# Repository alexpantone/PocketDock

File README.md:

# PocketDock
The Pocket Dock modular synthesizer system and associated modules

Licensed under CERN-OHL-P-2.0

The base Pocket Dock is designed to take the +/-12v audio and control voltage of a Eurorack or Pocket Rack synthesizer system and safely shift them down to interface with a Pocket Operator, while giving it a nice little cradle to sit in a modular system. I've also made other modules to fit the Pocket Rack standard. These are all still very much in progress. The Dock is based on interfacing with the Pocket Operator via pogo pins, but that has not proved to be reliable in testing; I'm looking for better solutions.

Here's a rundown of the modules.
## Power Distro
#### Not tested
Provide Molex connectors to split power to other Pocket Rack modules, with reverse polarity protection.
## Buffered Mult
#### Tested: works great
two 1-to-3 buffered multipliers in one module. The second input is normaled to the first, so when nothing is connected to Input 2, it acts as a 1-to-6 mult. This module also doubles as an unbuffered passive mult by not populating any components besides the jacks and closing all the solder jumpers.
## Clock Skipper
#### Tested: works on a breadboard, current PCB version has no audio output
A simple version of a gate sequencer that uses an incoming clock signal, and mutes or unmutes the signal based on a small bank of DIP switches.
##Noise Hits
#### Not tested
White, pink, and blue noise generator with a simple transistor VCA on each channel to act as a simple drum machine.
## Nyblcore and Pikocore
#### My PCBs are untested
A version of Infinite Digit's [Nyblcore](https://github.com/schollz/nyblcore) and [Pikocore](https://infinitedigits.co/docs/products/pikocore/) refactored into the Pocket Rack size.
## Pocket Socket
#### Not tested
A base for prototyping new modules. All the jacks and power circuitry are on the main module, and the actual audio passes onto a daughterboard with pin headers.
## Quant
#### Not tested
a Seeed Studio Xiao-based quantizer. I haven't started the firmware on this yet.

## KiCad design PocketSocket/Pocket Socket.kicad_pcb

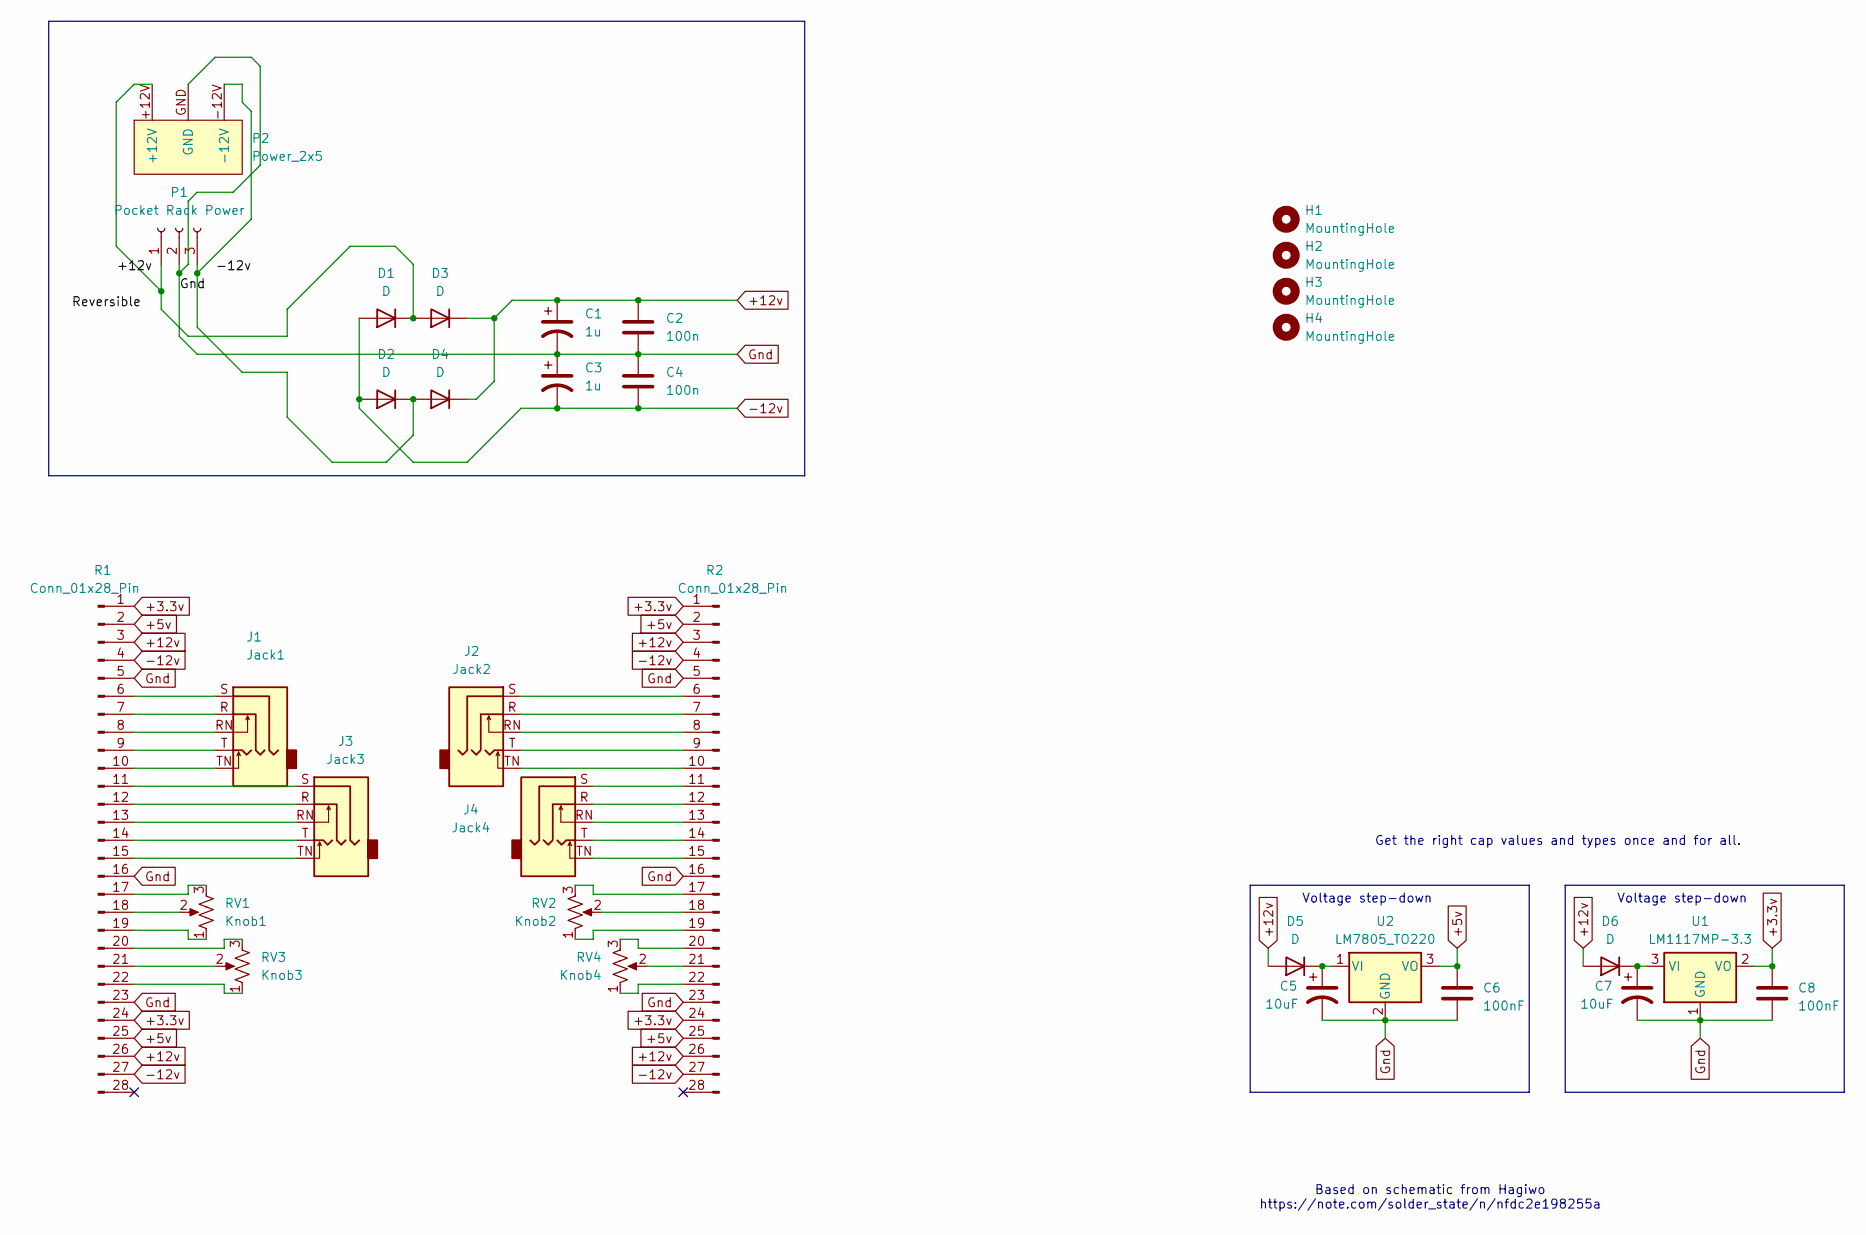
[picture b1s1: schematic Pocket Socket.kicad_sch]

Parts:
C1, C3: 1u; CP_EIA-3216-10_Kemet-I_Pad1.58x1.35mm_HandSolder
C2, C4: 100n; C_0805_2012Metric_Pad1.18x1.45mm_HandSolder
C5, C7: 10uF; C_0805_2012Metric_Pad1.18x1.45mm_HandSolder
C6, C8: 100nF; C_0805_2012Metric_Pad1.18x1.45mm_HandSolder
D1, D2, D3, D4, D5, D6: D; D_0805_2012Metric_Pad1.15x1.40mm_HandSolder
H1, H2, H3, H4: MountingHole; MountingHole_2.2mm_M2
J1: Jack1; Jack_3.5mm_QingPu_WQP-PJ358
J2: Jack2; Jack_3.5mm_QingPu_WQP-PJ358
J3: Jack3; Jack_3.5mm_QingPu_WQP-PJ358
J4: Jack4; Jack_3.5mm_QingPu_WQP-PJ358
P1: Pocket Rack Power; Molex_SL_171971-0003_1x03_P2.54mm_Vertical
P2: Power_2x5; Power_2x5_Vertical
R1, R2: Conn_01x28_Pin; PinHeader_1x28_P2.54mm_Vertical
RV1: Knob1; Potentiometer_Alpha_RD901F-40-00D_Single_Vertical
RV2: Knob2; Potentiometer_Alpha_RD901F-40-00D_Single_Vertical
RV3: Knob3; Potentiometer_Alpha_RD901F-40-00D_Single_Vertical
RV4: Knob4; Potentiometer_Alpha_RD901F-40-00D_Single_Vertical
U1: LM1117MP-3.3; SOT-223-3_TabPin2
U2: LM7805_TO220; SOT-223-3_TabPin2

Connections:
+3.3v: C8.1, R1.1, R1.24, R2.1, R2.24, U1.2 (VO)
+5v: C6.1, R1.2, R1.25, R2.2, R2.25, U2.3 (VO)
+12v: C1.1, C2.1, D3.1 (K), D4.1 (K), D5.2 (A), D6.2 (A), R1.3, R1.26, R2.3, R2.26
-12v: C3.2, C4.2, D1.2 (A), D2.2 (A), R1.4, R1.27, R2.4, R2.27
Gnd: C1.2, C2.2, C3.1, C4.1, C5.2, C6.2, C7.2, C8.2, P1.2, P2.GND, R1.5, R1.16, R1.23, R2.5, R2.16, R2.23, U1.1 (GND), U2.2 (GND)
unnamed: D1.1 (K), D3.2 (A), P1.1, P2.+12V
unnamed: D2.1 (K), D4.2 (A), P1.3, P2.-12V
unnamed: C5.1, D5.1 (K), U2.1 (VI)
unnamed: C7.1, D6.1 (K), U1.3 (VI)
unnamed: J1.S, R1.6
unnamed: J1.R, R1.7
unnamed: J1.RN, R1.8
unnamed: J1.T, R1.9
unnamed: J1.TN, R1.10
unnamed: J3.S, R1.11
unnamed: J3.R, R1.12
unnamed: J3.RN, R1.13
unnamed: J3.T, R1.14
unnamed: J3.TN, R1.15
unnamed: R1.17, RV1.3
unnamed: R1.18, RV1.2
unnamed: R1.19, RV1.1
unnamed: R1.20, RV3.3
unnamed: R1.21, RV3.2
unnamed: R1.22, RV3.1
unnamed: J2.S, R2.6
unnamed: J2.R, R2.7
unnamed: J2.RN, R2.8
unnamed: J2.T, R2.9
unnamed: J2.TN, R2.10
unnamed: J4.S, R2.11
unnamed: J4.R, R2.12
unnamed: J4.RN, R2.13
unnamed: J4.T, R2.14
unnamed: J4.TN, R2.15
unnamed: R2.17, RV2.3
unnamed: R2.18, RV2.2
unnamed: R2.19, RV2.1
unnamed: R2.20, RV4.3
unnamed: R2.21, RV4.2
unnamed: R2.22, RV4.1

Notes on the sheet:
Voltage step-down
Get the right cap values and types once and for all.
Based on schematic from Hagiwo https://note.com/solder_state/n/nfdc2e198255a

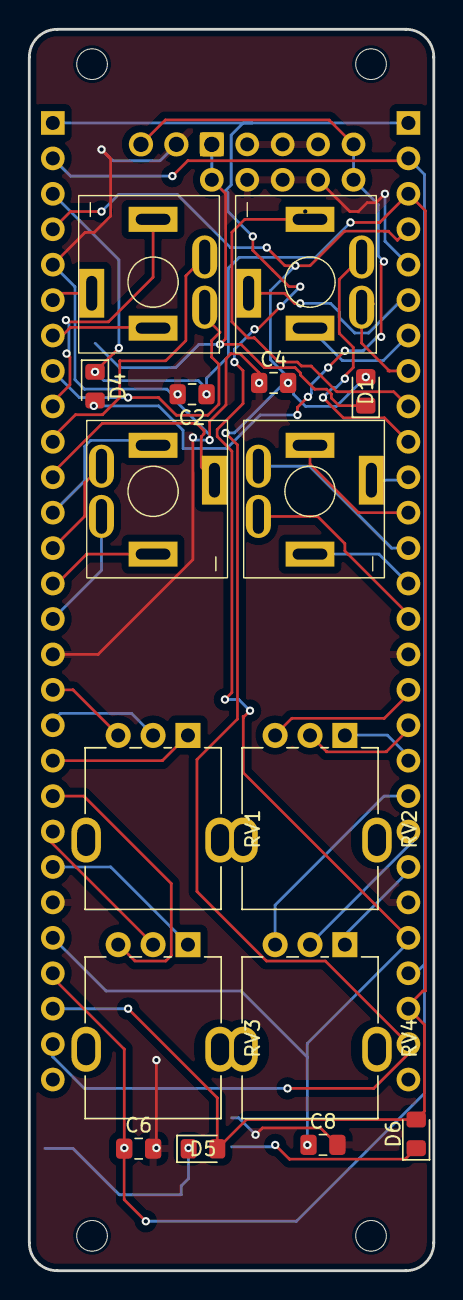
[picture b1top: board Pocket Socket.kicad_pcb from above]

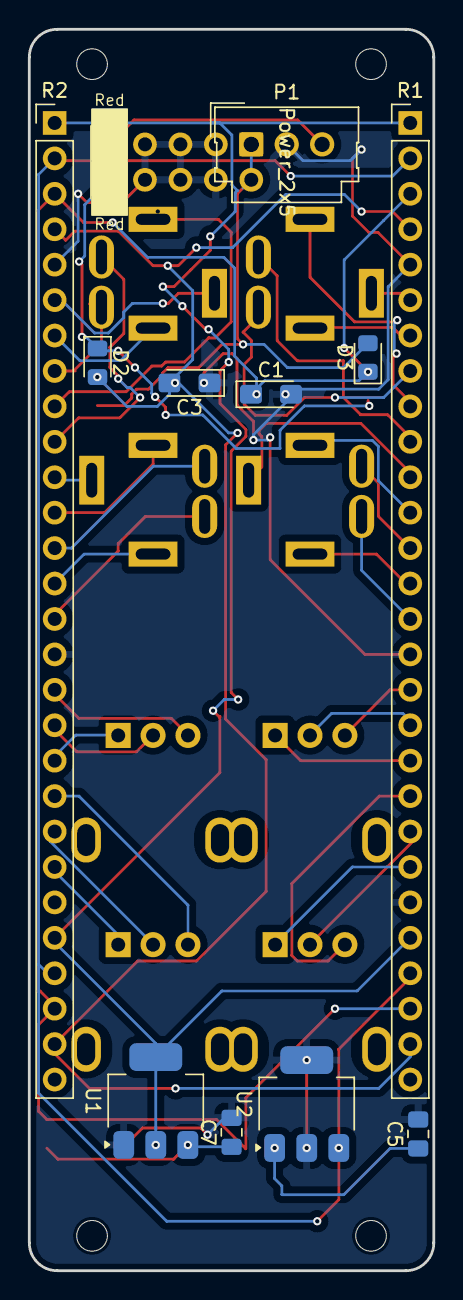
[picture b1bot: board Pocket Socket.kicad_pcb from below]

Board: 2 copper layers, 29.0 x 89.0 mm, 32 parts (12 on the bottom side), 41 nets.

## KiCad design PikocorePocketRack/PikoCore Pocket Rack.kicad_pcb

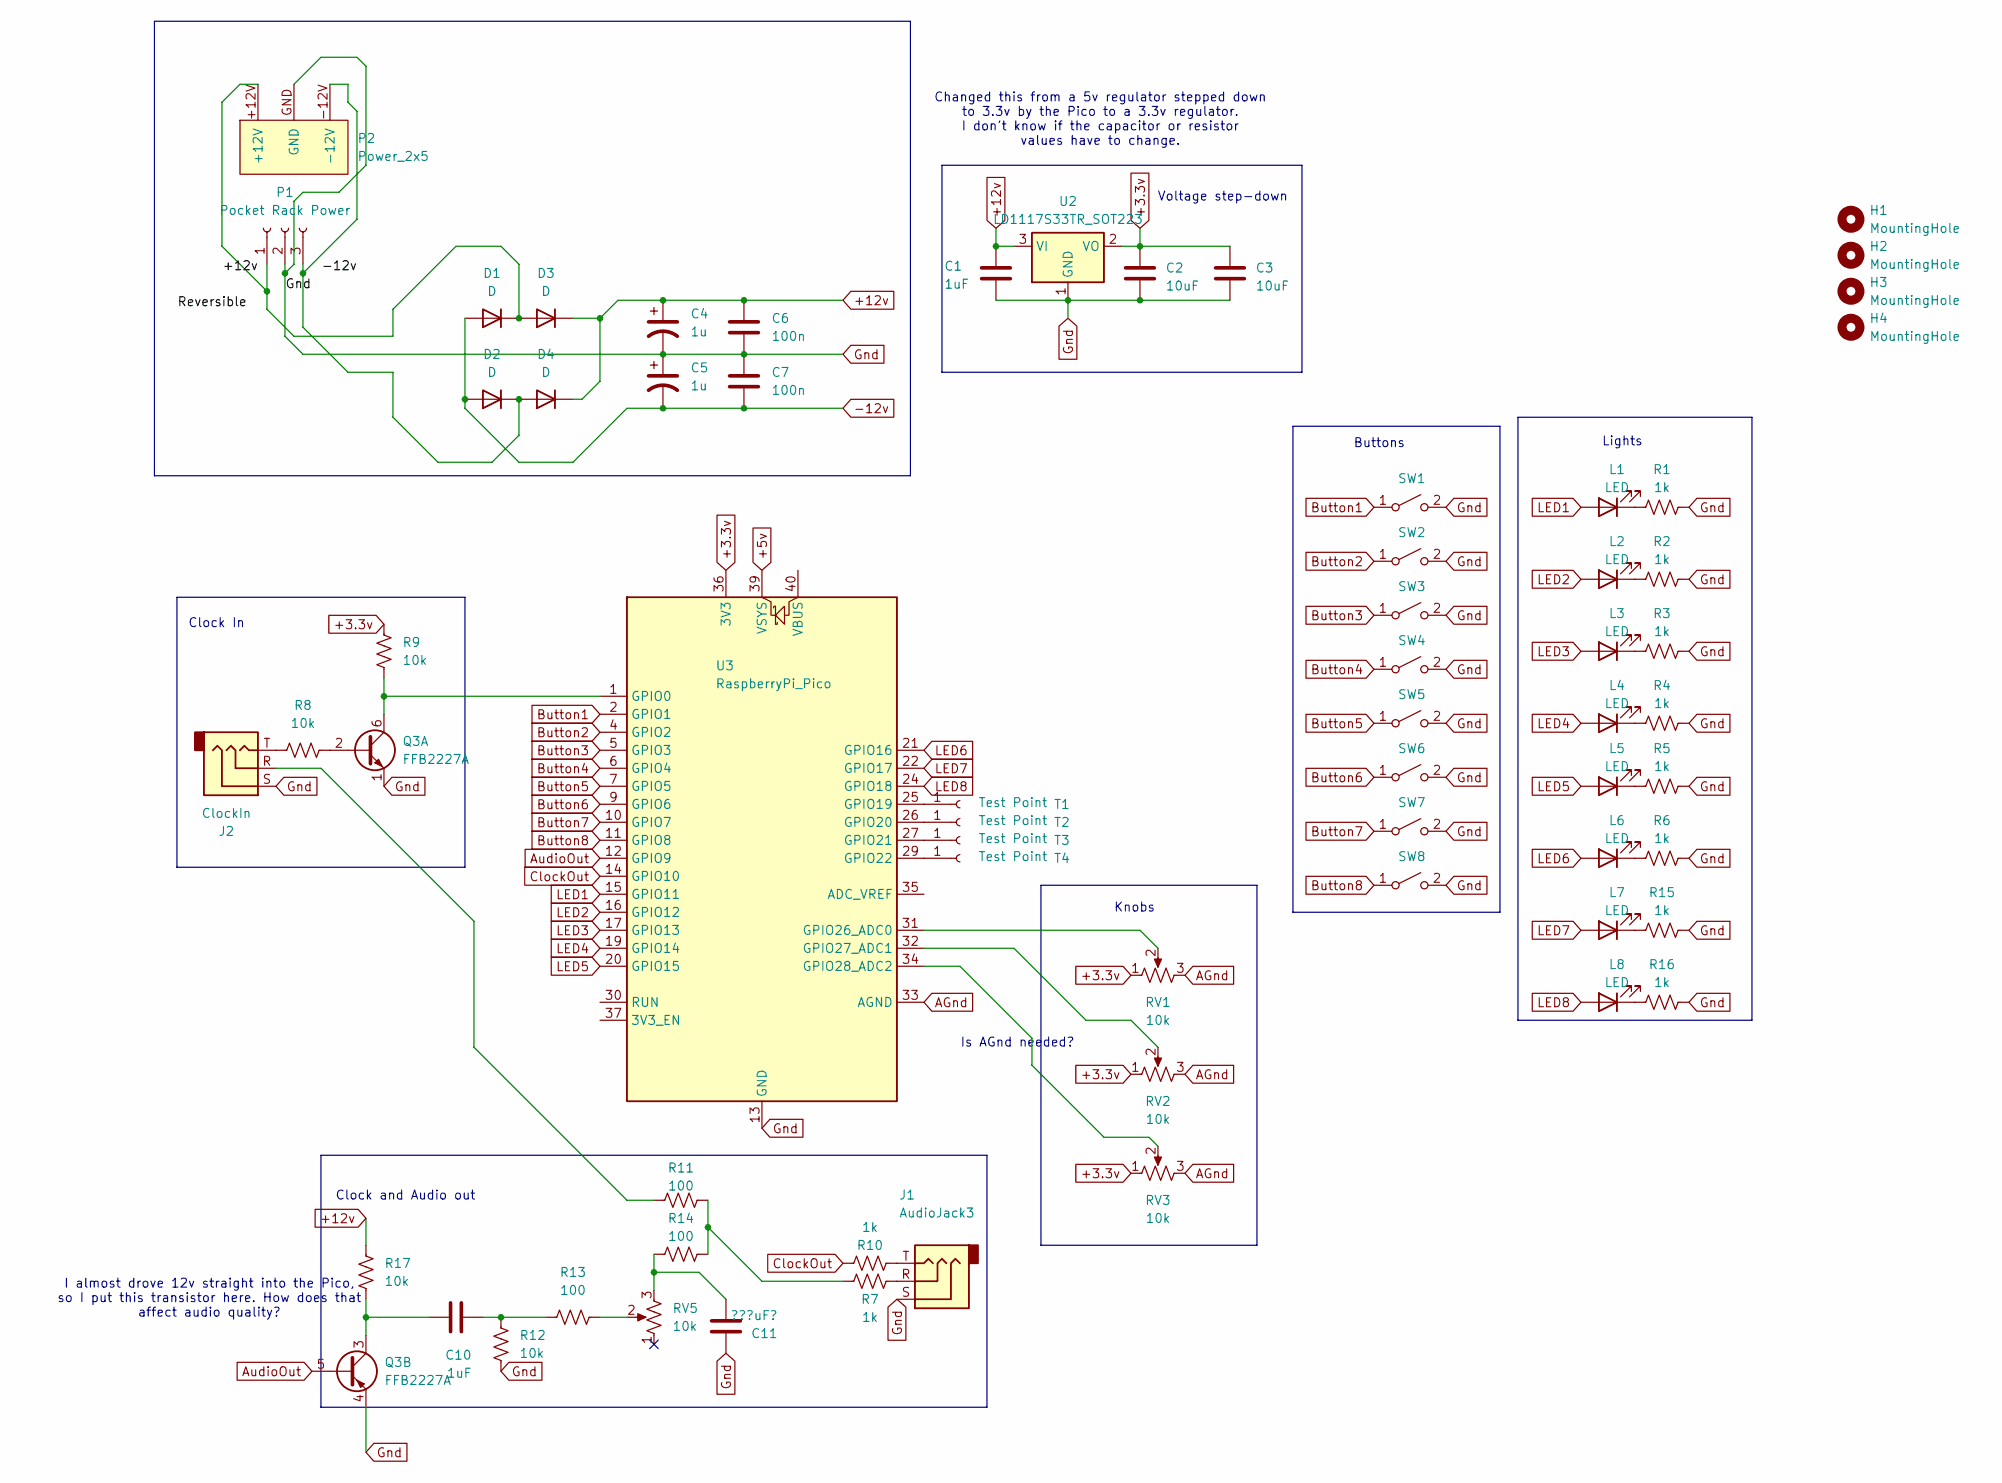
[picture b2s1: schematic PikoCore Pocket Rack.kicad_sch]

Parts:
C1, C10: 1uF; C_0805_2012Metric_Pad1.18x1.45mm_HandSolder
C2, C3: 10uF; C_0805_2012Metric_Pad1.18x1.45mm_HandSolder
C4, C5: 1u; CP_EIA-3216-10_Kemet-I_Pad1.58x1.35mm_HandSolder
C6, C7: 100n; C_0805_2012Metric_Pad1.18x1.45mm_HandSolder
C11: ???uF?; C_0805_2012Metric_Pad1.18x1.45mm_HandSolder
D1, D2, D3, D4: D; D_0805_2012Metric_Pad1.15x1.40mm_HandSolder
H1, H2, H3, H4: MountingHole; MountingHole_2.2mm_M2
J1: AudioJack3; Jack_3.5mm_QingPu_WQP-PJ301CM
J2: ClockIn; Jack_3.5mm_QingPu_WQP-PJ301CM
L1, L2, L3, L4, L5, L6, L7, L8: LED; LED_0805_2012Metric_Pad1.15x1.40mm_HandSolder
P1: Pocket Rack Power; Molex_SL_171971-0003_1x03_P2.54mm_Vertical
P2: Power_2x5; Power_2x5_Vertical
Q3: FFB2227A; SOT-363_SC-70-6
R1, R2, R3, R4, R5, R6, R7, R10, R15, R16: 1k; R_0805_2012Metric_Pad1.20x1.40mm_HandSolder
R8, R9, R12, R17: 10k; R_0805_2012Metric_Pad1.20x1.40mm_HandSolder
R11, R13, R14: 100; R_0805_2012Metric_Pad1.20x1.40mm_HandSolder
RV1, RV2, RV3, RV5: 10k; Potentiometer_Alpha_RD901F-40-00D_Single_Vertical
SW1, SW2, SW3, SW4, SW5, SW6, SW7, SW8: SW_SPST; SW_Push_1P1T_NO_6x6mm_H9.5mm
T1, T2, T3, T4: Test Point; TestPoint_Plated_Hole_D2.0mm
U2: LD1117S33TR_SOT223; SOT-223-3_TabPin2
U3: RaspberryPi_Pico; RaspberryPi_Pico_Common

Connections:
+3.3v: C2.1, C3.1, R9.2, RV1.1, RV2.1, RV3.1, U2.2 (VO), U3.36 (3V3)
+5v: U3.39 (VSYS)
+12v: C1.1, C4.1, C6.1, D3.1 (K), D4.1 (K), R17.2, U2.3 (VI)
-12v: C5.2, C7.2, D1.2 (A), D2.2 (A)
AGnd: RV1.3, RV2.3, RV3.3, U3.33 (AGND)
AudioOut: Q3.5 (B2), U3.12 (GPIO9)
Button1: SW1.1 (A), U3.2 (GPIO1)
Button2: SW2.1 (A), U3.4 (GPIO2)
Button3: SW3.1 (A), U3.5 (GPIO3)
Button4: SW4.1 (A), U3.6 (GPIO4)
Button5: SW5.1 (A), U3.7 (GPIO5)
Button6: SW6.1 (A), U3.9 (GPIO6)
Button7: SW7.1 (A), U3.10 (GPIO7)
Button8: SW8.1 (A), U3.11 (GPIO8)
ClockOut: R10.2, U3.14 (GPIO10)
Gnd: C1.2, C2.2, C3.2, C4.2, C5.1, C6.2, C7.1, C11.1, J1.S, J2.S, P1.2, P2.GND, Q3.1 (E1), Q3.4 (E2), R1.2, R2.2, R3.2, R4.2, R5.2, R6.2, R12.1, R15.2, R16.2, SW1.2 (B), SW2.2 (B), SW3.2 (B), SW4.2 (B), SW5.2 (B), SW6.2 (B), SW7.2 (B), SW8.2 (B), U2.1 (GND), U3.3 (GND), U3.8 (GND), U3.13 (GND), U3.18 (GND), U3.23 (GND), U3.28 (GND), U3.38 (GND)
LED1: L1.2 (A), U3.15 (GPIO11)
LED2: L2.2 (A), U3.16 (GPIO12)
LED3: L3.2 (A), U3.17 (GPIO13)
LED4: L4.2 (A), U3.19 (GPIO14)
LED5: L5.2 (A), U3.20 (GPIO15)
LED6: L6.2 (A), U3.21 (GPIO16)
LED7: L7.2 (A), U3.22 (GPIO17)
LED8: L8.2 (A), U3.24 (GPIO18)
unnamed: C10.2, R12.2, R13.2
unnamed: C11.2, R14.2, RV5.3
unnamed: D1.1 (K), D3.2 (A), P1.1, P2.+12V
unnamed: D2.1 (K), D4.2 (A), P1.3, P2.-12V
unnamed: J1.R, R7.2
unnamed: J1.T, R10.1
unnamed: J2.R, R11.1
unnamed: J2.T, R8.1
unnamed: L1.1 (K), R1.1
unnamed: L2.1 (K), R2.1
unnamed: L3.1 (K), R3.1
unnamed: L4.1 (K), R4.1
unnamed: L5.1 (K), R5.1
unnamed: L6.1 (K), R6.1
unnamed: L7.1 (K), R15.1
unnamed: L8.1 (K), R16.1
unnamed: Q3.2 (B1), R8.2
unnamed: Q3.6 (C1), R9.1, U3.1 (GPIO0)
unnamed: C10.1, Q3.3 (C2), R17.1
unnamed: R7.1, R11.2, R14.1
unnamed: R13.1, RV5.2
unnamed: T1.1, U3.25 (GPIO19)
unnamed: T2.1, U3.26 (GPIO20)
unnamed: T3.1, U3.27 (GPIO21)
unnamed: T4.1, U3.29 (GPIO22)
unnamed: RV1.2, U3.31 (GPIO26_ADC0)
unnamed: RV2.2, U3.32 (GPIO27_ADC1)
unnamed: RV3.2, U3.34 (GPIO28_ADC2)

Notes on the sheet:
Is AGnd needed?
Clock and Audio out
Lights
I almost drove 12v straight into the Pico, so I put this transistor here. How does that affect audio quality?
Knobs
Buttons
Voltage step-down
Changed this from a 5v regulator stepped down to 3.3v by the Pico to a 3.3v regulator. I don't know if the capacitor or resistor values have to change.
Clock In

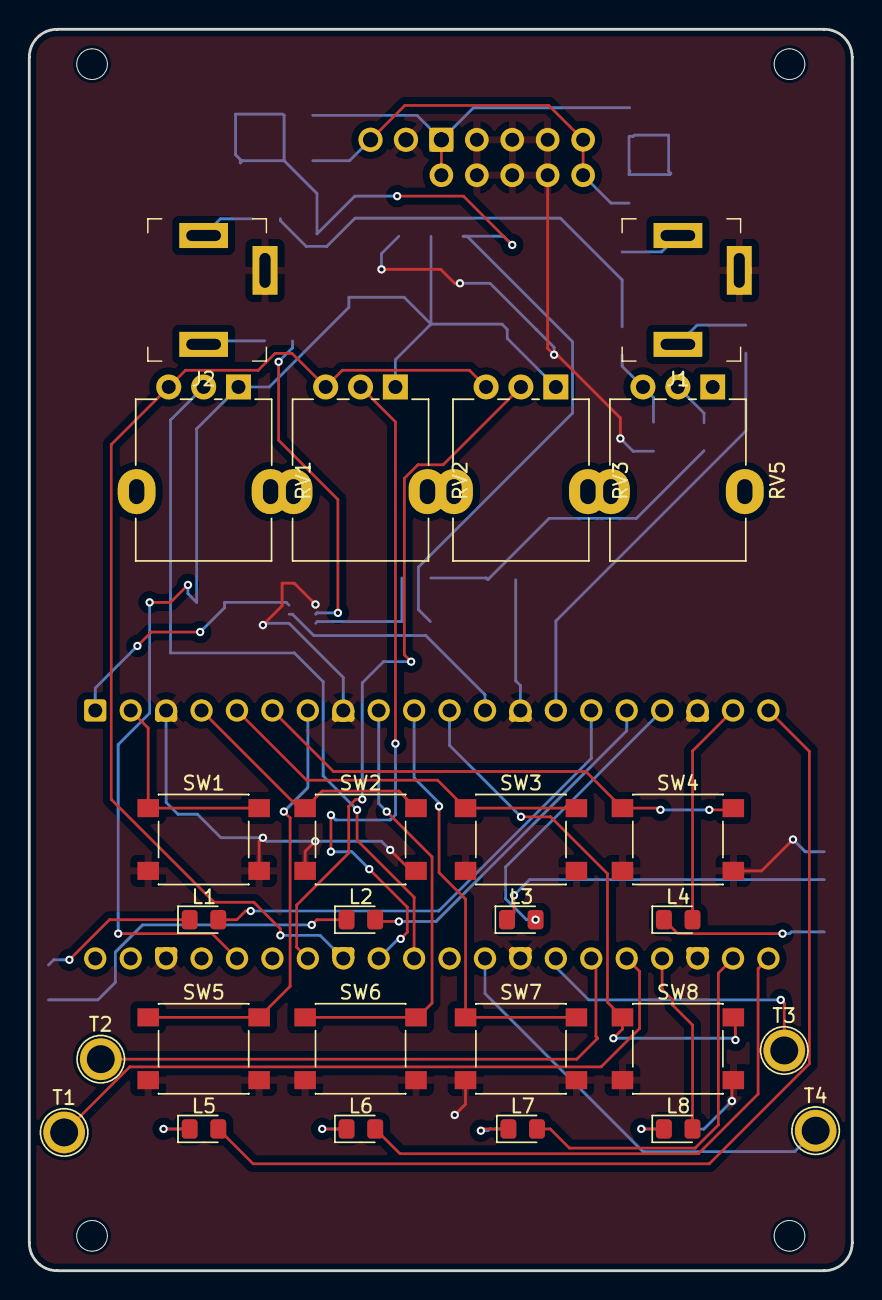
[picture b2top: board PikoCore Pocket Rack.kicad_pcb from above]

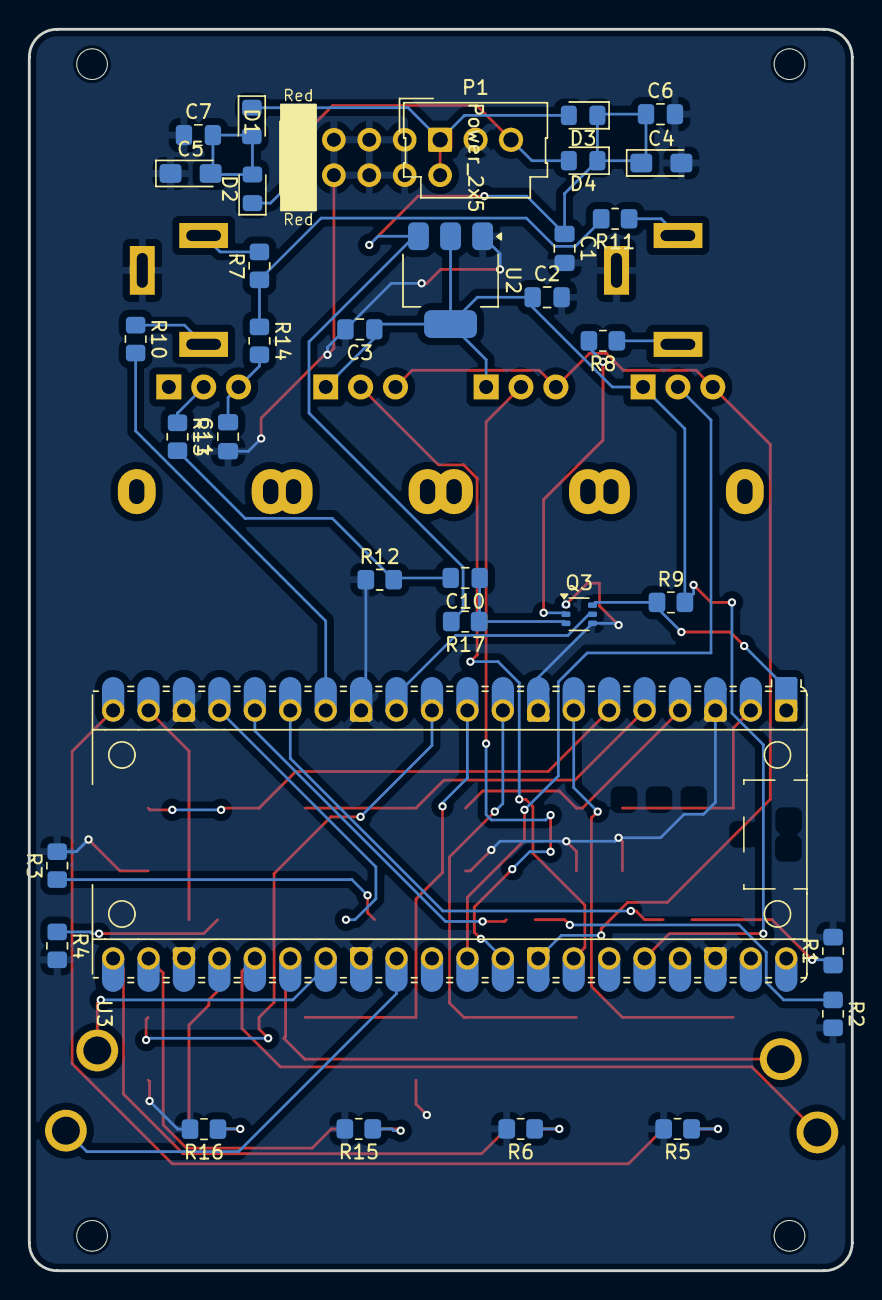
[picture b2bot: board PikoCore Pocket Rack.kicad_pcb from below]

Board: 2 copper layers, 59.0 x 89.0 mm, 65 parts (35 on the bottom side), 51 nets.

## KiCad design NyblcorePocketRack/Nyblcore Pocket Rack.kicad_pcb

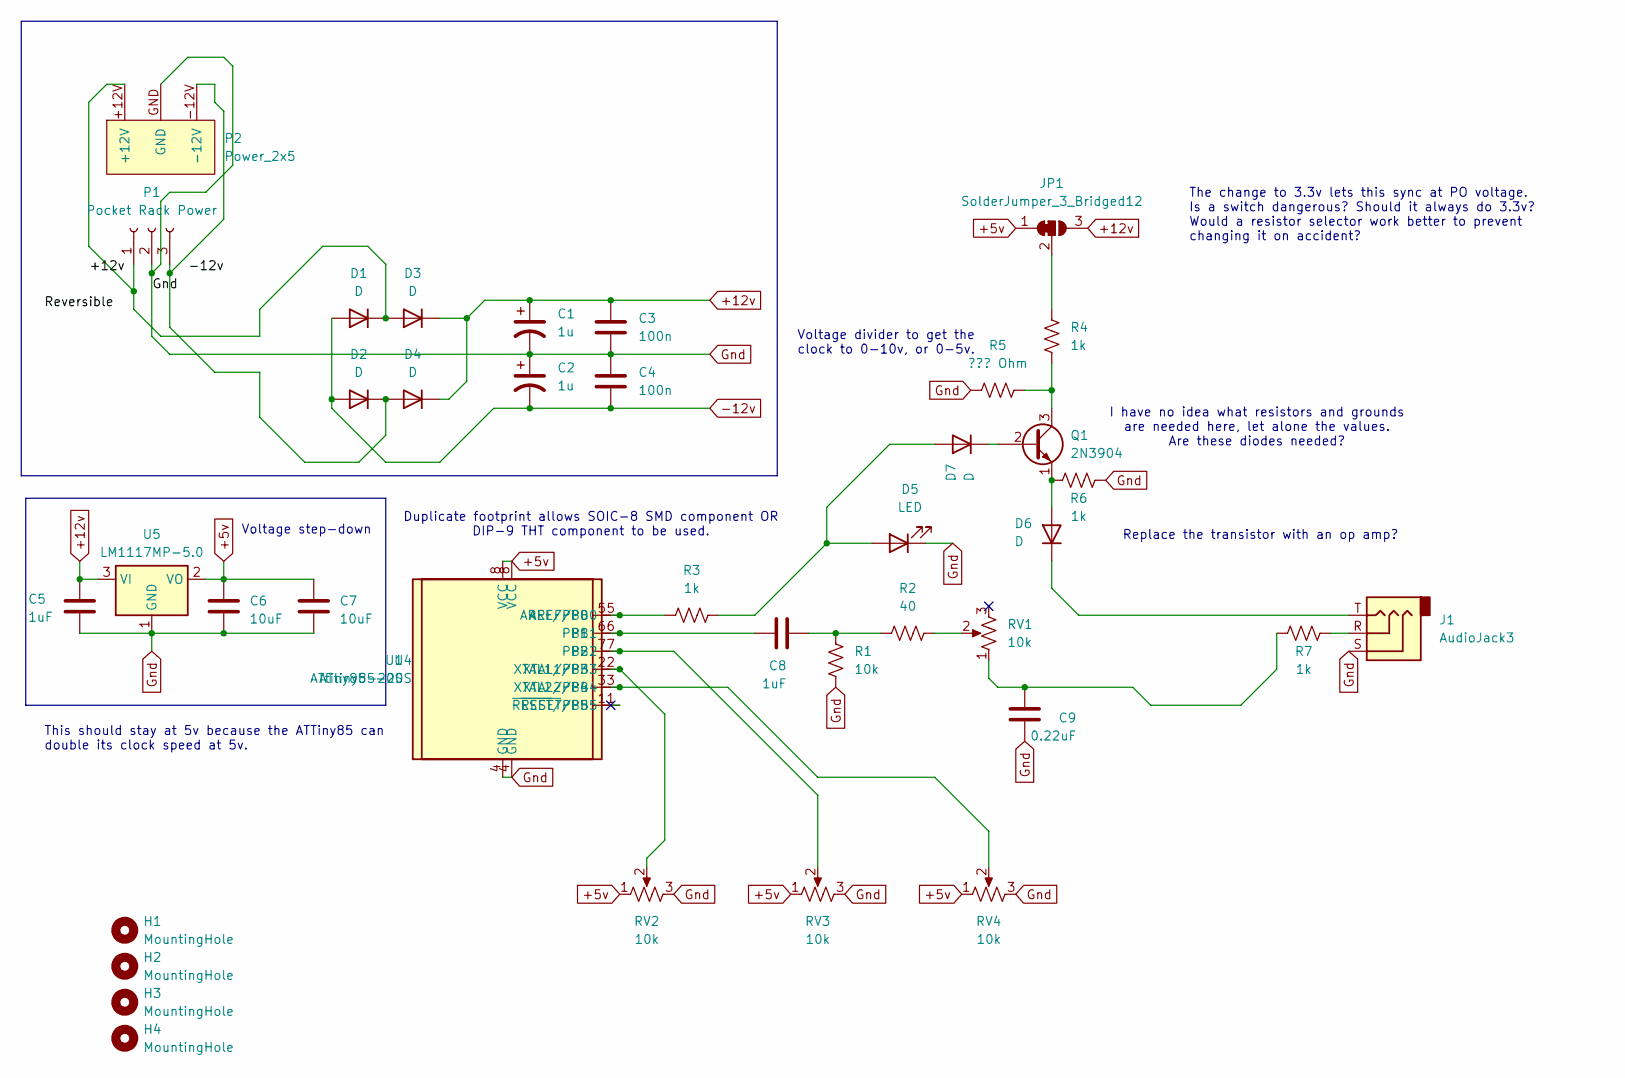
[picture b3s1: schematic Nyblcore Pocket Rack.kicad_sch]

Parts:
C1, C2: 1u; CP_EIA-3216-10_Kemet-I_Pad1.58x1.35mm_HandSolder
C3, C4: 100n; C_0805_2012Metric_Pad1.18x1.45mm_HandSolder
C5, C8: 1uF; C_0805_2012Metric_Pad1.18x1.45mm_HandSolder
C6, C7: 10uF; C_0805_2012Metric_Pad1.18x1.45mm_HandSolder
C9: 0.22uF; C_0805_2012Metric_Pad1.18x1.45mm_HandSolder
D1, D2, D3, D4, D6, D7: D; D_0805_2012Metric_Pad1.15x1.40mm_HandSolder
D5: LED; LED_D3.0mm
H1, H2, H3, H4: MountingHole; MountingHole_2.2mm_M2
J1: AudioJack3; Jack_3.5mm_QingPu_WQP-PJ301CM
JP1: SolderJumper_3_Bridged12; SolderJumper-3_P1.3mm_Bridged12_Pad1.0x1.5mm
P1: Pocket Rack Power; Molex_SL_171971-0003_1x03_P2.54mm_Vertical
P2: Power_2x5; Power_2x5_Vertical
Q1: 2N3904; TO-92_Inline
R1: 10k; R_0805_2012Metric_Pad1.20x1.40mm_HandSolder
R2: 40; R_0805_2012Metric_Pad1.20x1.40mm_HandSolder
R3, R4, R6, R7: 1k; R_0805_2012Metric_Pad1.20x1.40mm_HandSolder
R5: ??? Ohm; R_0805_2012Metric_Pad1.20x1.40mm_HandSolder
RV1, RV2, RV3, RV4: 10k; Potentiometer_Alpha_RD901F-40-00D_Single_Vertical
U1: ATtiny85-20S; DIP-8_W7.62mm
U4: ATtiny85-20S; SOIC-8W_5.3x5.3mm_P1.27mm
U5: LM1117MP-5.0; SOT-223-3_TabPin2

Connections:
+5v: C6.1, C7.1, JP1.1 (A), RV2.1, RV3.1, RV4.1, U1.8 (VCC), U4.8 (VCC), U5.2 (VO)
+12v: C1.1, C3.1, C5.1, D3.1 (K), D4.1 (K), JP1.3 (B), U5.3 (VI)
-12v: C2.2, C4.2, D1.2 (A), D2.2 (A)
Gnd: C1.2, C2.1, C3.2, C4.1, C5.2, C6.2, C7.2, C9.1, D5.1 (K), J1.S, P1.2, P2.GND, R1.2, R5.2, R6.2, RV2.3, RV3.3, RV4.3, U1.4 (GND), U4.4 (GND), U5.1 (GND)
unnamed: C8.2, R1.1, R2.1
unnamed: C9.2, R7.1, RV1.1
unnamed: D1.1 (K), D3.2 (A), P1.1, P2.+12V
unnamed: D2.1 (K), D4.2 (A), P1.3, P2.-12V
unnamed: D5.2 (A), D7.2 (A), R3.2
unnamed: D6.2 (A), Q1.1 (E), R6.1
unnamed: D6.1 (K), J1.T
unnamed: D7.1 (K), Q1.2 (B)
unnamed: J1.R, R7.2
unnamed: JP1.2 (C), R4.2
unnamed: Q1.3 (C), R4.1, R5.1
unnamed: R2.2, RV1.2
unnamed: R3.1, U1.5 (AREF/PB0), U4.5 (AREF/PB0)
unnamed: C8.1, U1.6 (PB1), U4.6 (PB1)
unnamed: RV3.2, U1.7 (PB2), U4.7 (PB2)
unnamed: RV2.2, U1.2 (XTAL1/PB3), U4.2 (XTAL1/PB3)
unnamed: RV4.2, U1.3 (XTAL2/PB4), U4.3 (XTAL2/PB4)

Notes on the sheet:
Duplicate footprint allows SOIC-8 SMD component OR DIP-9 THT component to be used.
Replace the transistor with an op amp?
Voltage step-down
Voltage divider to get the clock to 0-10v, or 0-5v.
This should stay at 5v because the ATTiny85 can double its clock speed at 5v.
I have no idea what resistors and grounds are needed here, let alone the values. Are these diodes needed?
The change to 3.3v lets this sync at PO voltage. Is a switch dangerous? Should it always do 3.3v? Would a resistor selector work better to prevent changing it on accident?

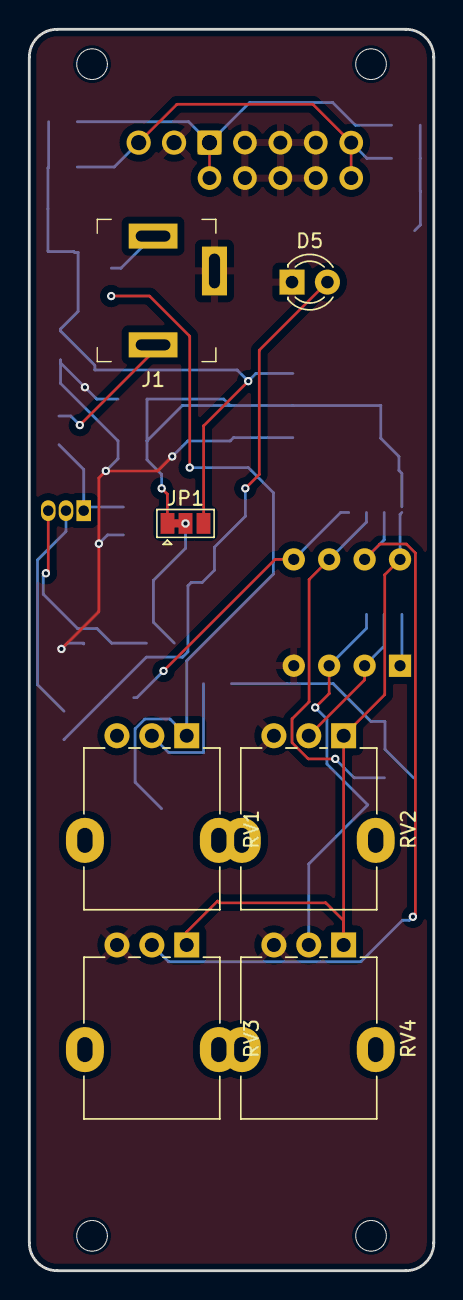
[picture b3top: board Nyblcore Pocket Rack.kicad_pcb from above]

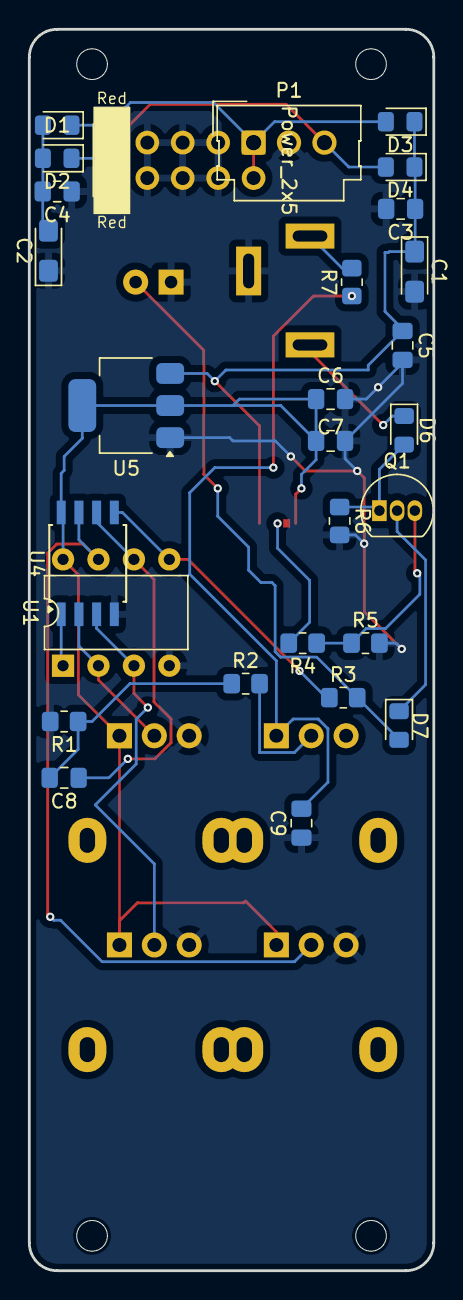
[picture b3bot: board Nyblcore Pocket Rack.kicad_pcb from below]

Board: 2 copper layers, 29.0 x 89.0 mm, 39 parts (28 on the bottom side), 21 nets.

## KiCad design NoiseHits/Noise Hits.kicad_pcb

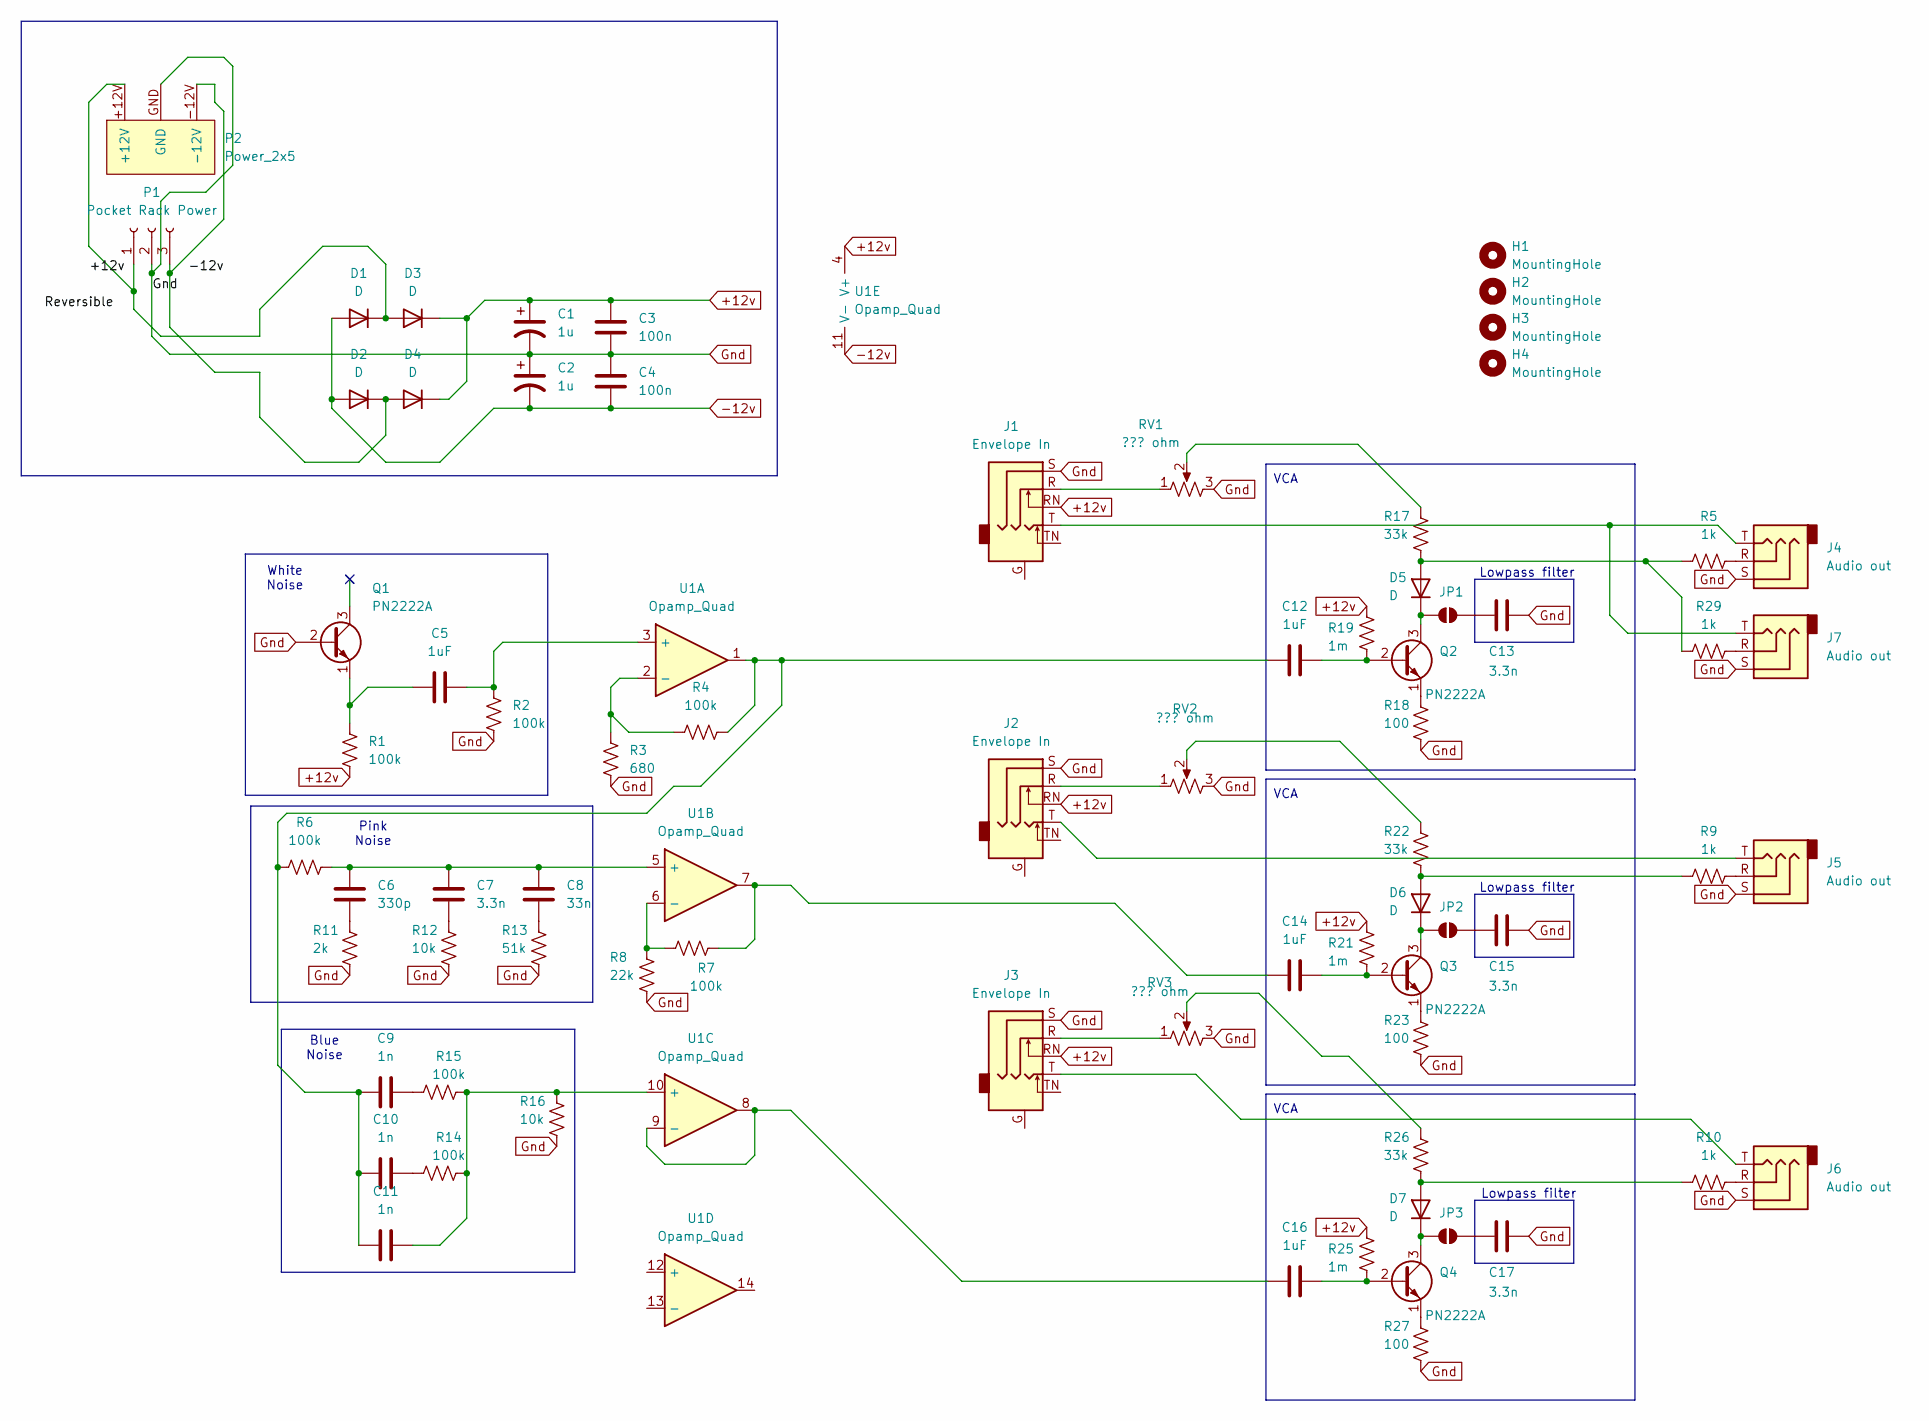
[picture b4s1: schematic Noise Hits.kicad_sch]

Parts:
C1, C2: 1u; CP_EIA-3216-10_Kemet-I_Pad1.58x1.35mm_HandSolder
C3, C4: 100n; C_0805_2012Metric_Pad1.18x1.45mm_HandSolder
C5, C12, C14, C16: 1uF; C_0805_2012Metric_Pad1.18x1.45mm_HandSolder
C6: 330p; C_0805_2012Metric_Pad1.18x1.45mm_HandSolder
C7, C13, C15, C17: 3.3n; C_0805_2012Metric_Pad1.18x1.45mm_HandSolder
C8: 33n; C_0805_2012Metric_Pad1.18x1.45mm_HandSolder
C9, C10, C11: 1n; C_0805_2012Metric_Pad1.18x1.45mm_HandSolder
D1, D2, D3, D4, D5, D6, D7: D; D_0805_2012Metric_Pad1.15x1.40mm_HandSolder
H1, H2, H3, H4: MountingHole; MountingHole_2.2mm_M2
J1, J2, J3: Envelope In; Jack_3.5mm_QingPu_WQP-PJ358
J4, J5, J6, J7: Audio out; Jack_3.5mm_QingPu_WQP-PJ301CM
JP1, JP2, JP3: SolderJumper_2_Open; SolderJumper-2_P1.3mm_Open_RoundedPad1.0x1.5mm
P1: Pocket Rack Power; Molex_SL_171971-0003_1x03_P2.54mm_Vertical
P2: Power_2x5; Power_2x5_Vertical
Q1, Q2, Q3, Q4: PN2222A; TO-92_Inline
R1, R2, R4, R6, R7, R14, R15: 100k; R_0805_2012Metric_Pad1.20x1.40mm_HandSolder
R3: 680; R_0805_2012Metric_Pad1.20x1.40mm_HandSolder
R5, R9, R10, R29: 1k; R_0805_2012Metric_Pad1.20x1.40mm_HandSolder
R8: 22k; R_0805_2012Metric_Pad1.20x1.40mm_HandSolder
R11: 2k; R_0805_2012Metric_Pad1.20x1.40mm_HandSolder
R12, R16: 10k; R_0805_2012Metric_Pad1.20x1.40mm_HandSolder
R13: 51k; R_0805_2012Metric_Pad1.20x1.40mm_HandSolder
R17, R22, R26: 33k; R_0805_2012Metric_Pad1.20x1.40mm_HandSolder
R18, R23, R27: 100; R_0805_2012Metric_Pad1.20x1.40mm_HandSolder
R19, R21, R25: 1m; R_0805_2012Metric_Pad1.20x1.40mm_HandSolder
RV1, RV2, RV3: ??? ohm; Potentiometer_Alpha_RD901F-40-00D_Single_Vertical
U1: Opamp_Quad; SOIC-14_3.9x8.7mm_P1.27mm

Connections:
+12v: C1.1, C3.1, D3.1 (K), D4.1 (K), J1.RN, J2.RN, J3.RN, R1.2, R19.2, R21.2, R25.2, U1.4 (V+)
-12v: C2.2, C4.2, D1.2 (A), D2.2 (A), U1.11 (V-)
Gnd: C1.2, C2.1, C3.2, C4.1, C13.1, C15.1, C17.1, J1.S, J2.S, J3.S, J4.S, J5.S, J6.S, J7.S, P1.2, P2.GND, Q1.2 (B), R2.2, R3.2, R8.1, R11.1, R12.1, R13.1, R16.1, R18.1, R23.1, R27.1, RV1.3, RV2.3, RV3.3
unnamed: C6.1, R11.2
unnamed: C7.1, R12.2
unnamed: C8.1, R13.2
unnamed: C9.2, R15.1
unnamed: C9.1, C10.1, C11.1, C12.1, R4.2, R6.1, U1.1
unnamed: C10.2, R14.1
unnamed: C14.1, R7.2, U1.7
unnamed: D1.1 (K), D3.2 (A), P1.1, P2.+12V
unnamed: D2.1 (K), D4.2 (A), P1.3, P2.-12V
unnamed: D5.2 (A), R5.1, R17.1, R29.1
unnamed: D5.1 (K), JP1.1 (A), Q2.3 (C)
unnamed: D6.2 (A), R9.1, R22.1
unnamed: D6.1 (K), JP2.1 (A), Q3.3 (C)
unnamed: D7.2 (A), R10.1, R26.1
unnamed: D7.1 (K), JP3.1 (A), Q4.3 (C)
unnamed: J1.R, RV1.1
unnamed: J1.T, J4.T, J7.T
unnamed: J2.R, RV2.1
unnamed: J2.T, J5.T
unnamed: J3.R, RV3.1
unnamed: J3.T, J6.T
unnamed: J4.R, R5.2
unnamed: J5.R, R9.2
unnamed: J6.R, R10.2
unnamed: J7.R, R29.2
unnamed: C13.2, JP1.2 (B)
unnamed: C15.2, JP2.2 (B)
unnamed: C17.2, JP3.2 (B)
unnamed: C5.1, Q1.1 (E), R1.1
unnamed: C12.2, Q2.2 (B), R19.1
unnamed: Q2.1 (E), R18.2
unnamed: C14.2, Q3.2 (B), R21.1
unnamed: Q3.1 (E), R23.2
unnamed: C16.2, Q4.2 (B), R25.1
unnamed: Q4.1 (E), R27.2
unnamed: R17.2, RV1.2
unnamed: R22.2, RV2.2
unnamed: R26.2, RV3.2
unnamed: C5.2, R2.1, U1.3 (+)
unnamed: R3.1, R4.1, U1.2 (-)
unnamed: C6.2, C7.2, C8.2, R6.2, U1.5 (+)
unnamed: R7.1, R8.2, U1.6 (-)
unnamed: C11.2, R14.2, R15.2, R16.2, U1.10 (+)
unnamed: C16.1, U1.8, U1.9 (-)

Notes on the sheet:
Lowpass filter
VCA
White Noise
Pink Noise
Blue Noise
